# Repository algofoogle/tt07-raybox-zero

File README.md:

# raybox-zero for TT07 (Tiny Tapeout 07) - Resubmission updated from TT04

This is a resubmission of a very simple ray caster demo (sort of like Wolf3D rendering) driving a VGA display without a framebuffer (i.e. by 'racing the beam').

It was originally submitted to TT04, but due to a synthesis bug in the OpenLane flow, it produced severely glitchy output that I didn't discover until the chips came back from fabrication. Had I run a GL (gate-level) sim back in the day, I probably would've caught it, but maybe not had much I could do about it.

The version of OpenLane that TT07 uses doesn't seem to exhibit the same problem; I've since implemented GL sim, and both been able to prove the TT04 bug, and prove that it is gone in this TT07 version. NOTE: Extra special thanks goes to Uri Shaked and Matt Venn of [Tiny Tapeout](https://tinytapeout.com). The opportunity to do this was largely supported by the two of them, who graciously offered a resubmission after the TT04 synthesis bug (from OpenLane) had been observed to cause severe glitches in the rendering (due to an unintended alteration of the logic).

For more information:
- [Read the documentation for this project](docs/info.md) (WIP; [open an issue](https://github.com/algofoogle/tt07-raybox-zero/issues) to tell me what more you want to know)
- See the main source repo for this project: [algofoogle/raybox-zero]
- See [my journal](https://github.com/algofoogle/journal/blob/master/0204-2024-05-25.md) with some details about how I work on this locally.

[algofoogle/raybox-zero]: https://github.com/algofoogle/raybox-zero

## What is Tiny Tapeout?

Tiny Tapeout is an educational project that aims to make it easier and cheaper than ever to get your digital and analog designs manufactured on a real chip.

To learn more and get started, visit https://tinytapeout.com.

## Resources

- [FAQ](https://tinytapeout.com/faq/)
- [Digital design lessons](https://tinytapeout.com/digital_design/)
- [Learn how semiconductors work](https://tinytapeout.com/siliwiz/)
- [Join the community](https://tinytapeout.com/discord)
- [Build your design locally](https://docs.google.com/document/d/1aUUZ1jthRpg4QURIIyzlOaPWlmQzr-jBn3wZipVUPt4)

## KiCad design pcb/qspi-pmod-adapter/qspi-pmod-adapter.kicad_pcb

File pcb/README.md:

# tt07-raybox-zero PCB(s)

This directory currently contains:

*   [`qspi-pmod-adapter/`](./qspi-pmod-adapter): Kicad PCB layout for a small adapter board that makes the [Tiny QSPI PMOD] work with tt07-raybox-zero. Can also just be used as a QSPI PMOD (if you solder U1 and C1).
*   [`Anton Kicad Footprints Lib.pretty/`](./Anton%20Kicad%20Footprints%20Lib.pretty/): Kicad footprints for PMOD connectors.

# Where to get the latest versions?

Each PCB and each revision I've had made has its own unique URL suffix silkscreened on the board.

For the latest version's files, see: https://github.com/algofoogle/tt07-raybox-zero/tree/main/pcb

Otherwise, see the [PCB revisions below](#pcb-revisions) to compare with the specific revision you have.

# PCB revisions

## `tt07a` QSPI adapter

This version of the board was my first prototype, intended to be demonstrated during the Tiny Tapeout 7 Bring-up Party live stream.

This board has a PMOD plug on only one end that is to remain plugged into the TT07 demo board's "Bidirectional" PMOD socket, and then the [Tiny QSPI PMOD] is meant to be alternated between the vertical slot (J2, for programming) and the edge slot (J3, for use with raybox-zero).

There is a footprint for an optional *on-board* QSPI chip, but it is not wired for being programmed by the [Tiny Tapeout Flasher](https://tinytapeout.github.io/tinytapeout-flasher/) utility, so would need to be wired up manually for programming.

[Commit `4ecdaab`](https://github.com/algofoogle/tt07-raybox-zero/tree/4ecdaabfdce3f8536820e55c5c4c37ef2575f69a/pcb/qspi-pmod-adapter) has the specific Gerber files that were fabricated.

[Tiny QSPI PMOD]: https://github.com/mole99/qspi-pmod

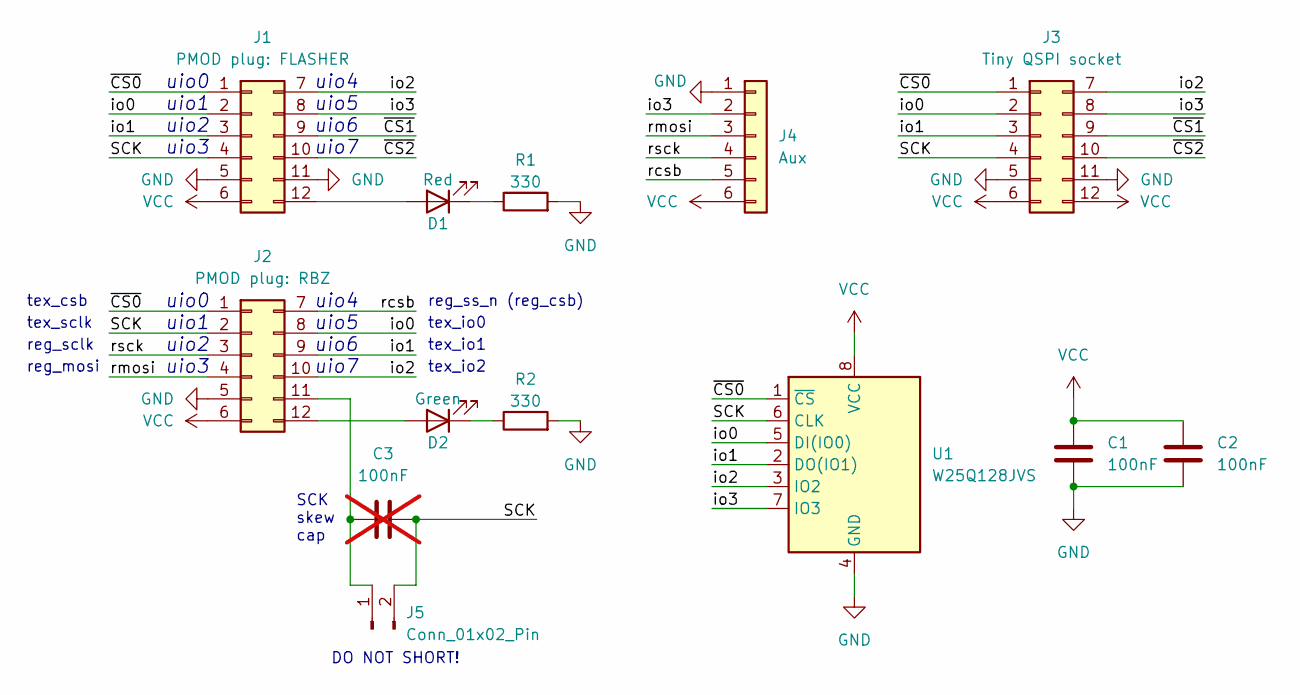
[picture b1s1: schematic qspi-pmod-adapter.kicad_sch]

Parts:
C1, C2: 100nF; C_0805_2012Metric_Pad1.18x1.45mm_HandSolder
C3: 100nF; C_0805_2012Metric_Pad1.18x1.45mm_HandSolder; not fitted
D1: Red; LED_0805_2012Metric_Pad1.15x1.40mm_HandSolder
D2: Green; LED_0805_2012Metric_Pad1.15x1.40mm_HandSolder
J1: PMOD plug: FLASHER; PinHeader_2x06_P2.54mm_PMODPeriph2B_Clip
J2: PMOD plug: RBZ; PinHeader_2x06_P2.54mm_PMODPeriph2B_Clip
J3: Tiny QSPI socket; PinSocket_2x06_P2.54mm_PMODPeriph2B_Vertical
J4: Aux; PinHeader_1x06_P2.54mm_Vertical
J5: Conn_01x02_Pin; PinHeader_1x02_P2.54mm_Vertical
R1, R2: 330; R_0805_2012Metric_Pad1.20x1.40mm_HandSolder
U1: W25Q128JVS; SOIC-8_5.23x5.23mm_P1.27mm

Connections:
/SCK: C3.2, J1.4, J2.2, J3.4, J5.2, U1.6 (CLK)
/io0: J1.2, J2.8, J3.2, U1.5 (DI(IO0))
/io1: J1.3, J2.9, J3.3, U1.2 (DO(IO1))
/io2: J1.7, J2.10, J3.7, U1.3 (IO2)
/io3: J1.8, J3.8, J4.2, U1.7 (IO3)
/rcsb: J2.7, J4.5
/rmosi: J2.4, J4.3
/rsck: J2.3, J4.4
/~CS0: J1.1, J2.1, J3.1, U1.1 (~CS)
/~CS1: J1.9, J3.9
/~CS2: J1.10, J3.10
GND: C1.2, C2.2, J1.5, J1.11, J2.5, J3.5, J3.11, J4.1, R1.2, R2.2, U1.4 (GND)
unnamed: D1.2 (A), J1.12
unnamed: D1.1 (K), R1.1
unnamed: D2.2 (A), J2.12
unnamed: D2.1 (K), R2.1
unnamed: C3.1, J2.11, J5.1
VCC: C1.1, C2.1, J1.6, J2.6, J3.6, J3.12, J4.6, U1.8 (VCC)

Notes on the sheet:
tex_sclk
tex_io1
uio4 uio5 uio6 uio7
DO NOT SHORT!
reg_ss_n (reg_csb)
uio0 uio1 uio2 uio3
tex_io0
reg_sclk
tex_io2
reg_mosi
SCK skew cap
tex_csb

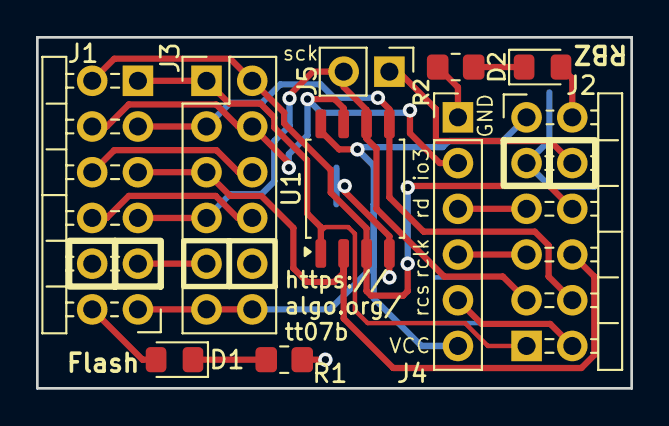
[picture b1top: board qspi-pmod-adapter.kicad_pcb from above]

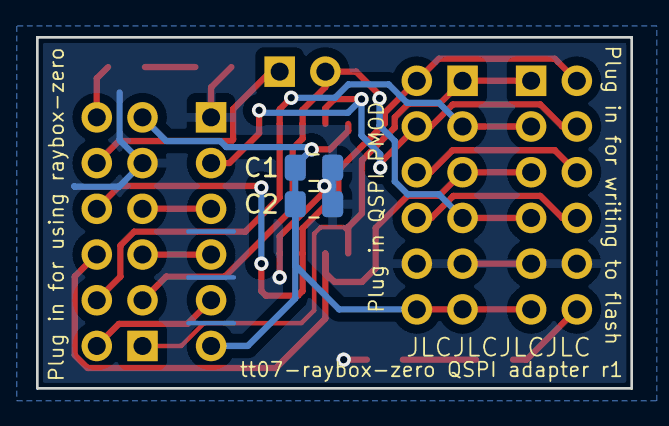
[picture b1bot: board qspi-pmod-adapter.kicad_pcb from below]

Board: 2 copper layers, 33.0 x 19.5 mm, 12 parts (2 on the bottom side), 18 nets.

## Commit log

2024-05-29 Add raybox-zero@1.0 submodule; TT07 plumbing; basic test; rough doco
2024-05-29 Update tests per TT07 standard; repo housekeeping
2024-05-30 Tidy test scripts [no ci]
2024-05-30 GHAs upload flies; Disable fpga GHA
2024-05-30 Add test/frames_out, hopefully fix GHA CI
2024-05-30 Trying to fix GHAs for storing frames
2024-05-30 Wire up raybox-zero '1.5'; RTL sim works. No harden yet
2024-05-30 1.5-dev: Bring updates from raybox-zero to fix unknown (x) states
2024-05-31 8x2 tiles test; tex ROM support inc. sim RTL+GL; pinout update
2024-05-31 1.5-dev: 6x2 tiles; SPI2 test example
2024-05-31 1.5-dev: Tiny fix for GHA tests
2024-05-31 1.5-dev: Fix another silly GHA test issue
2024-05-31 1.5-dev: Better tests inc. SPI coroutines; doco updates [no ci]
2024-05-31 1.5-dev: Shorter GHA GL test to save time [no ci]
2025-04-07 Tiny QSPI PMOD adapter PCB [no ci]
2025-04-27 README for tt07a PCB revision [no-ci]
2025-04-27 Pin ubuntu-22.04 for GitHub Actions
2025-04-27 tt07b (r1) PCB revision: QSPI adapter dual-plug [no ci]
